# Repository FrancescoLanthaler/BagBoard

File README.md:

# BagBoard

A cool macropad with an easy interface to allow you to change the keybinds to whatever you want!

## Get started:
First of all you will need the pcb and all the components.
Then you will need to install the libs and the main.py code.

### Web Interface:
https://bagboard.francescolanthaler.com/

#### Change Keypad Layout:
Inside the web interface you can reassign each Key to a specific value. 
If you want a key to output a string just use the *custom* option

To change the Layout then copy the code from the interface and replace the one in *main.py*

```python
keys_pressed = [Keycode.TWO, Keycode.A, Keycode.A, Keycode.FOUR, Keycode.FIVE, Keycode.SIX, Keycode.B, Keycode.SEVEN, Keycode.EIGHT, Keycode.NINE, Keycode.C, Keycode.PERIOD, Keycode.ZERO, Keycode.ENTER, Keycode.D]
rotary_pressed = ConsumerControlCode.PLAY_PAUSE
```

#### Change Animation:
To change the Gif just download one from any website or use a URL (has to be a "drawing" and it works best if black and white).
Then upload them to the site and when downloading it put it into the icons folder.

In the main.py change the file name and number of frame to the new ones:

```python
FRAMES = 9
IMAGE_FILE = "/icons/FILENAMEHERE.bmp".format(0)
```

## License:

Copyright 2024 Francesco Lanthaler
This project includes code from libraries that are licensed under various open-source licenses.

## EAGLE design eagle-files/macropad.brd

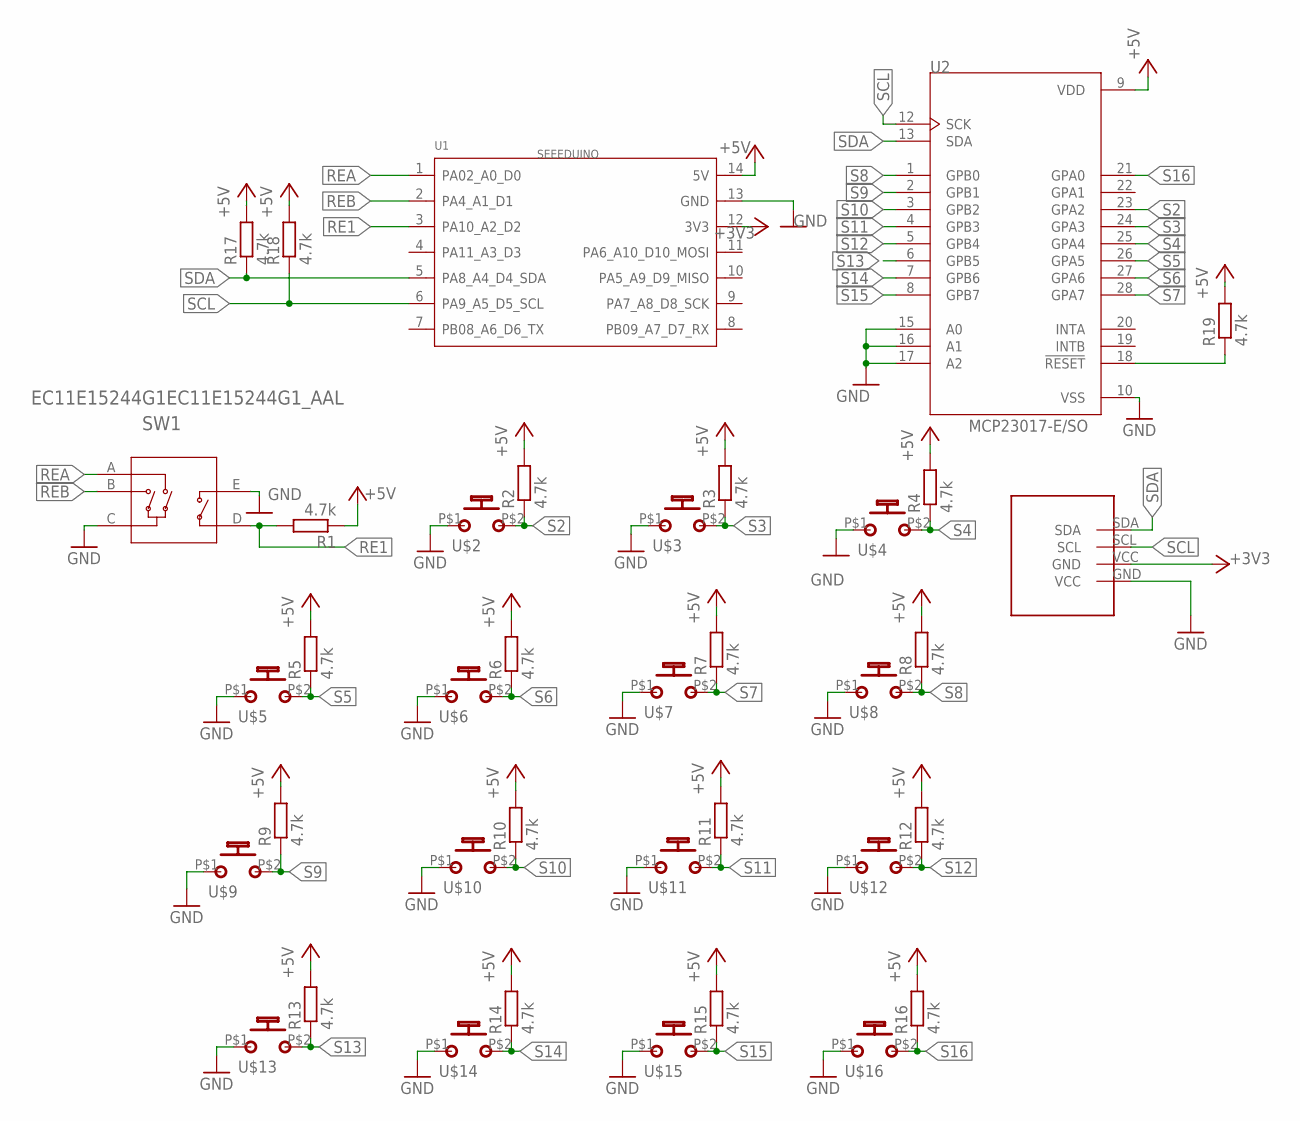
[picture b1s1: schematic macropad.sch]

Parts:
DISPLAY: OLED_0.96_I2C
R1, R2, R3, R4, R5, R6, R7, R8, R9, R10, R11, R12, R13, R14, R15, R16, R17, R18, R19: 4.7k; R0805
SW1: EC11E15244G1EC11E15244G1_AAL; EC11E15244G1_AAL
U1: SEEEDUINO; MOUDLE14P-2.54-21X17.8MM
U2: MCP23017-E/SO; SOIC127P1030X265-28N
U$2, U$3, U$4, U$5, U$6, U$7, U$8, U$9, U$10, U$11, U$12, U$13, U$14, U$15, U$16: MX1A-11NN; CHERRY_MX1A-11NN_SWITCH

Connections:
+3V3: DISPLAY.VCC (GND), U1.12 (3V3)
+5V: R1.1, R2.2, R3.2, R4.2, R5.2, R6.2, R7.2, R8.2, R9.2, R10.2, R11.2, R12.2, R13.2, R14.2, R15.2, R16.2, R17.2, R18.2, R19.2, U1.14 (5V), U2.9 (VDD)
GND: DISPLAY.GND (VCC), SW1.C, SW1.E, U1.13 (GND), U2.10 (VSS), U2.15 (A0), U2.16 (A1), U2.17 (A2), U$2.P$1, U$3.P$1, U$4.P$1, U$5.P$1, U$6.P$1, U$7.P$1, U$8.P$1, U$9.P$1, U$10.P$1, U$11.P$1, U$12.P$1, U$13.P$1, U$14.P$1, U$15.P$1, U$16.P$1
unnamed: R19.1, U2.18 (!RESET)
RE1: R1.2, SW1.D, U1.3 (PA10_A2_D2)
REA: SW1.A, U1.1 (PA02_A0_D0)
REB: SW1.B, U1.2 (PA4_A1_D1)
S2: R2.1, U2.23 (GPA2), U$2.P$2 (S)
S3: R3.1, U2.24 (GPA3), U$3.P$2 (S)
S4: R4.1, U2.25 (GPA4), U$4.P$2 (S)
S5: R5.1, U2.26 (GPA5), U$5.P$2 (S)
S6: R6.1, U2.27 (GPA6), U$6.P$2 (S)
S7: R7.1, U2.28 (GPA7), U$7.P$2 (S)
S8: R8.1, U2.1 (GPB0), U$8.P$2 (S)
S9: R9.1, U2.2 (GPB1), U$9.P$2 (S)
S10: R10.1, U2.3 (GPB2), U$10.P$2 (S)
S11: R11.1, U2.4 (GPB3), U$11.P$2 (S)
S12: R12.1, U2.5 (GPB4), U$12.P$2 (S)
S13: R13.1, U2.6 (GPB5), U$13.P$2 (S)
S14: R14.1, U2.7 (GPB6), U$14.P$2 (S)
S15: R15.1, U2.8 (GPB7), U$15.P$2 (S)
S16: R16.1, U2.21 (GPA0), U$16.P$2 (S)
SCL: DISPLAY.SCL, R18.1, U1.6 (PA9_A5_D5_SCL), U2.12 (SCK)
SDA: DISPLAY.SDA, R17.1, U1.5 (PA8_A4_D4_SDA), U2.13 (SDA)

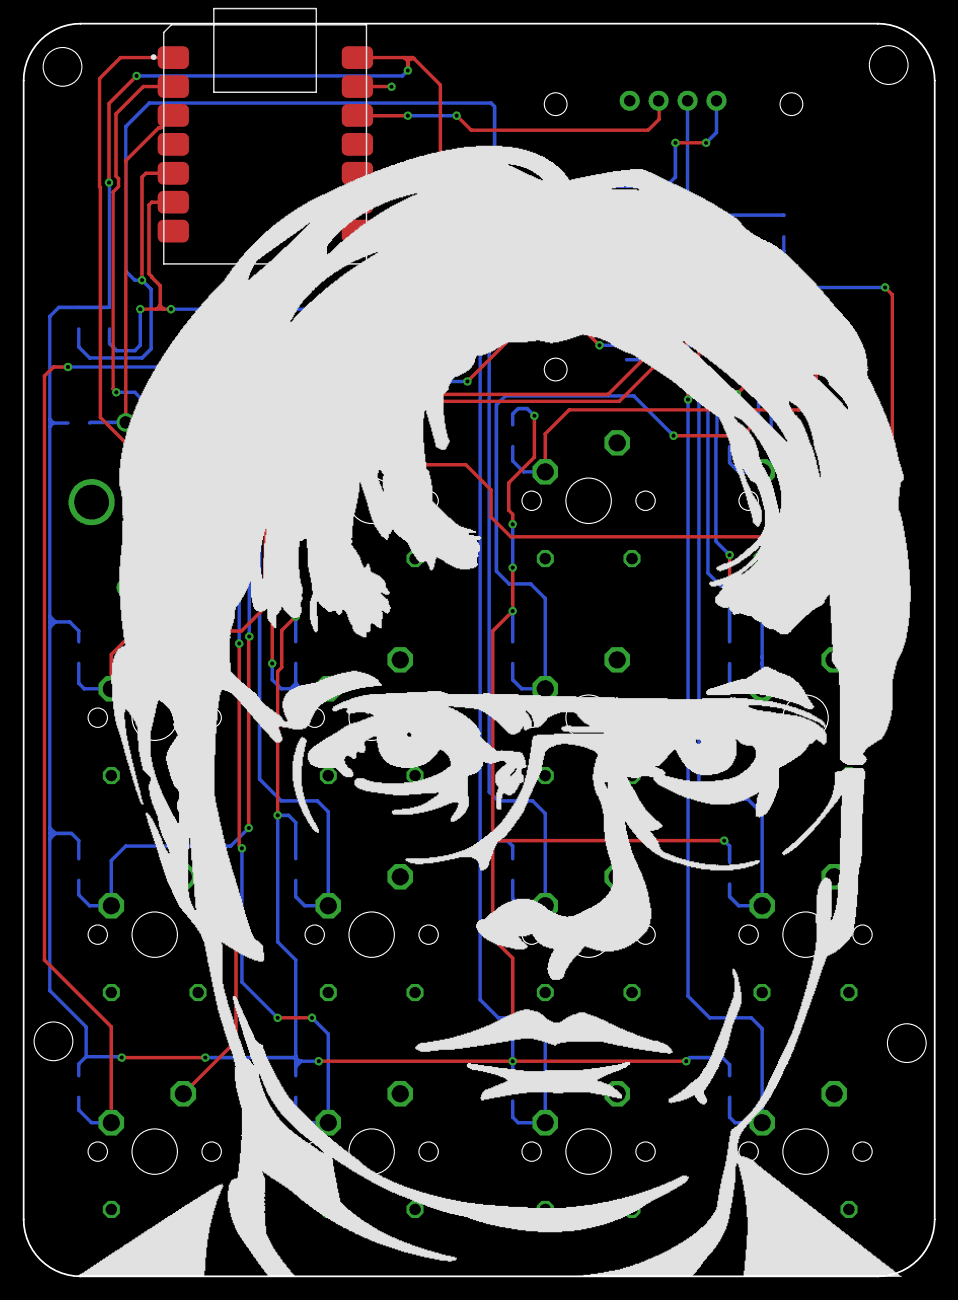
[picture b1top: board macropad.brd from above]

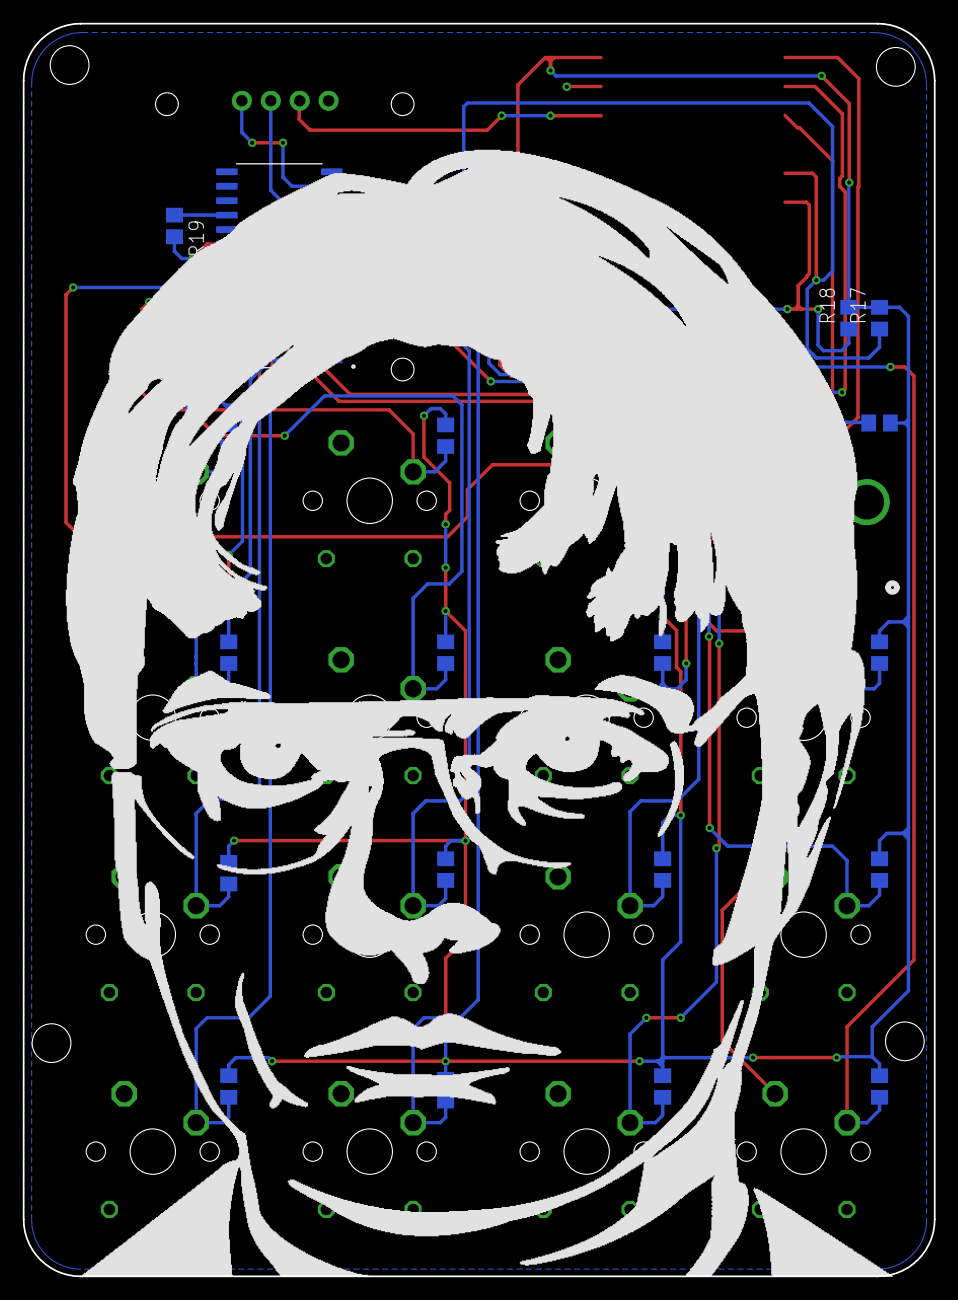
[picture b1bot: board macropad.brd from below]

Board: 2 copper layers, 80.0 x 110.0 mm, 38 parts (20 on the bottom side), 24 nets.

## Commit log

2023-10-18 Pushing code first time
2023-11-02 Added gitignore
2023-11-02 Fixed many things and expanded web interface to convert images
2023-11-03 Fixed gitignore
2023-11-03 .gitignore fix
2023-11-03 Made a design and fixed multiple things. Added possibility to use gifs from URL
2023-11-03 Edited .gitignore
2023-11-03 organized files in subfolders
2023-11-03 Code fixes
2023-11-03 Fixed url gif problems
2023-11-03 im a dumbass
2023-11-03 Deleted useless stuff
2023-11-03 Fixed javascript code
2023-11-04 Fixed issues with animation etc.
2023-11-08 Added boot file so it does not show up as usb and fixed interface
2023-11-08 Fixed name for website
2023-11-09 Worked a bit on design
2024-01-10 added 3d files for case
2024-11-16 fixing height and width
2024-11-16 fixing width and height
2024-11-16 fixing stuff

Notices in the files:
parts and their libraries:
COPYRIGHT: Copyright (C) 2023 Ultra Librarian. All rights reserved.
